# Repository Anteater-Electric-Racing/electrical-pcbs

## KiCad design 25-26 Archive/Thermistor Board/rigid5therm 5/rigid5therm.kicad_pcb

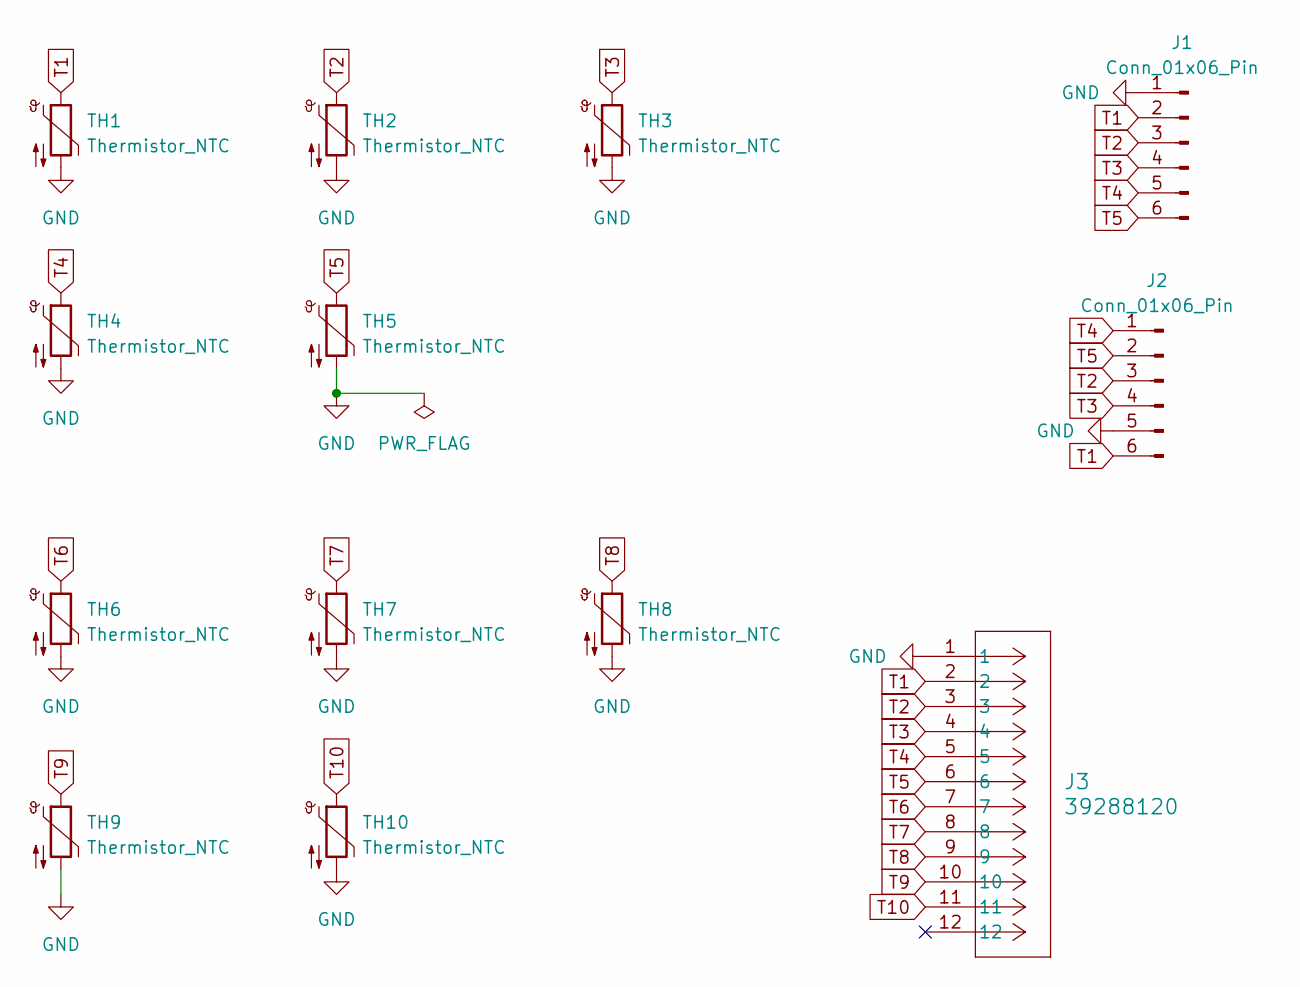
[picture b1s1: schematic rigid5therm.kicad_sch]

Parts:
J1, J2: Conn_01x06_Pin; PinHeader_2x03_P2.54mm_Vertical
J3: 39288120; CONN_SD-5566-002_12_MOL
TH1, TH2, TH3, TH4, TH5, TH6, TH7, TH8, TH9, TH10: Thermistor_NTC; Thermistor_NTCLE413

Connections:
GND: J1.1, J2.5, J3.1, TH1.2, TH2.2, TH3.2, TH4.2, TH5.2, TH6.2, TH7.2, TH8.2, TH9.2, TH10.2
T1: J1.2, J2.6, J3.2, TH1.1
T2: J1.3, J2.3, J3.3, TH2.1
T3: J1.4, J2.4, J3.4, TH3.1
T4: J1.5, J2.1, J3.5, TH4.1
T5: J1.6, J2.2, J3.6, TH5.1
T6: J3.7, TH6.1
T7: J3.8, TH7.1
T8: J3.9, TH8.1
T9: J3.10, TH9.1
T10: J3.11, TH10.1

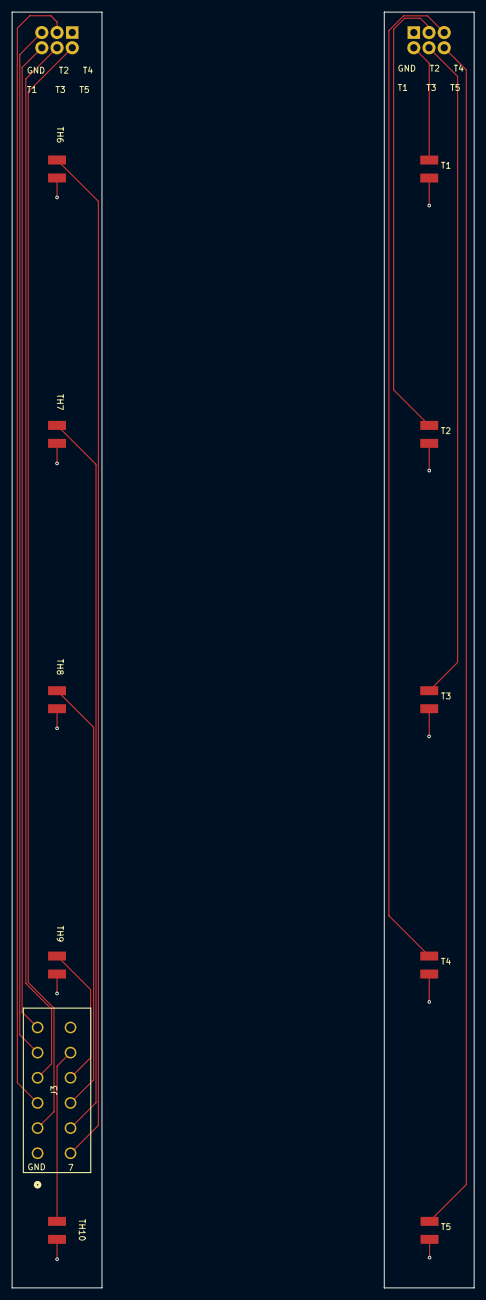
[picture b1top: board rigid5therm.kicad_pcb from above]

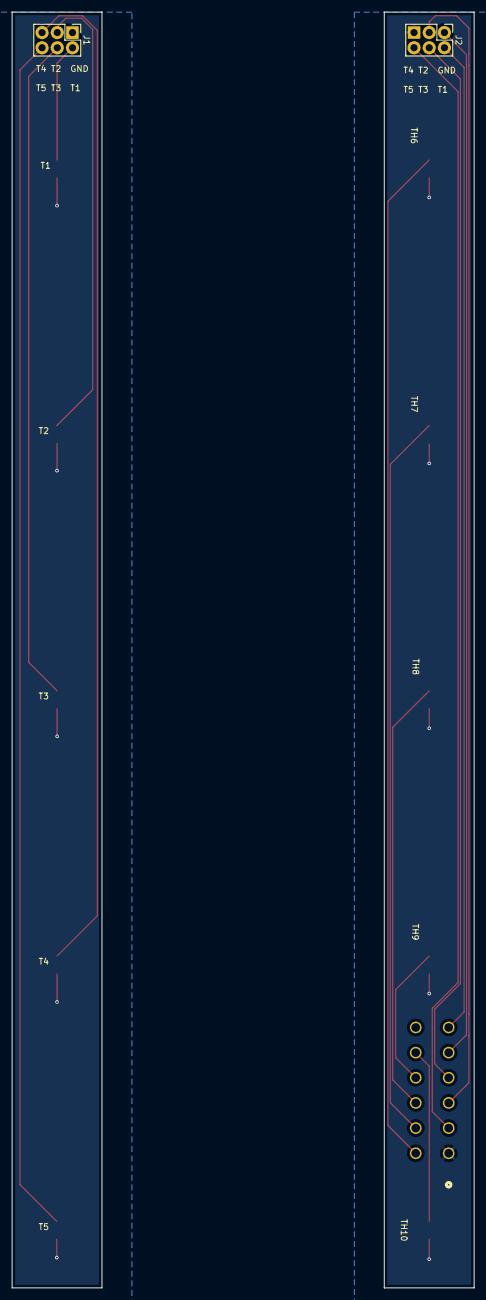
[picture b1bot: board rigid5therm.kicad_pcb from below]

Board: 2 copper layers, 77.1 x 213.0 mm, 13 parts (2 on the bottom side), 11 nets.

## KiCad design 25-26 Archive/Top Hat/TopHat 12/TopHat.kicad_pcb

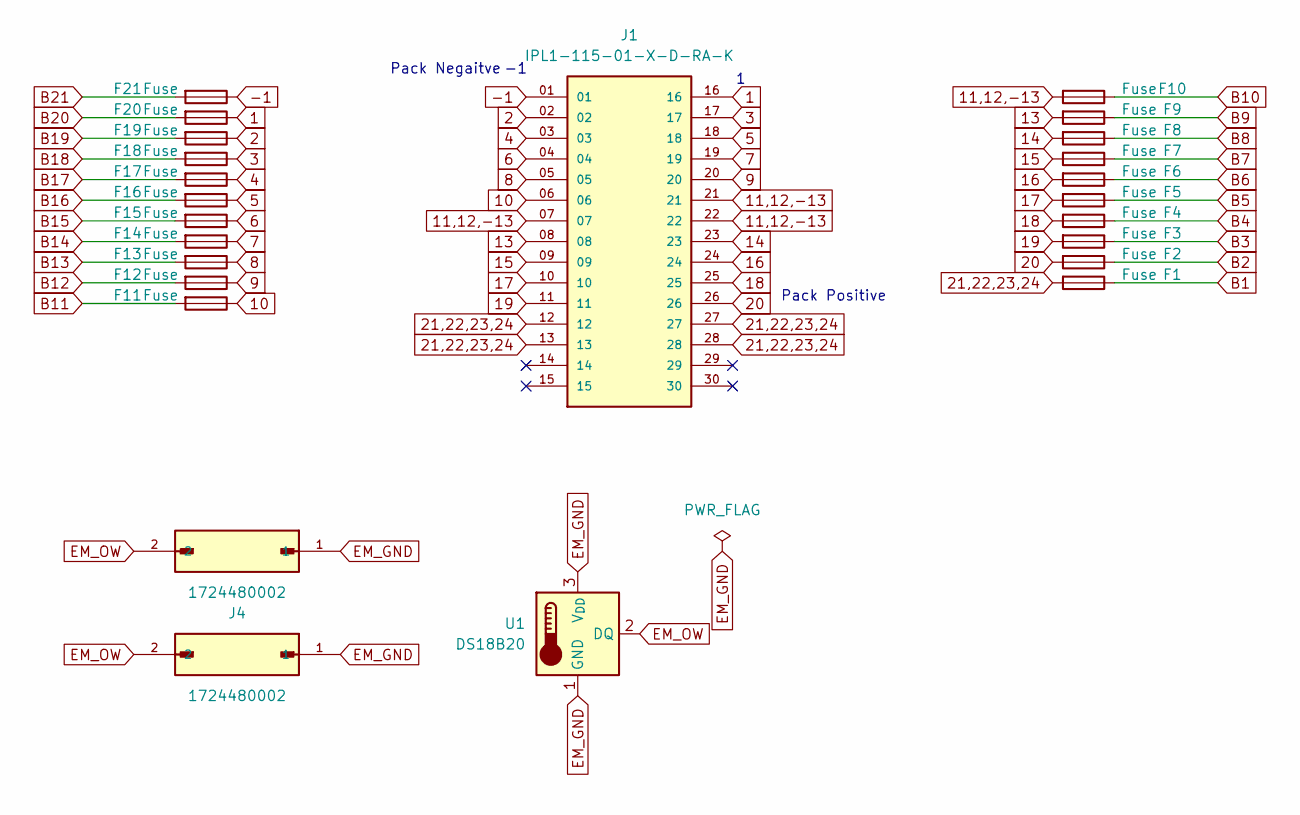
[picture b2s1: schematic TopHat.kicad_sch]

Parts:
F1, F2, F3, F4, F5, F6, F7, F8, F9, F10, F11, F12, F13, F14, F15, F16, F17, F18, F19, F20, F21: Fuse; FUSC6125X279N; MANUFACTURER PART NUMBER 0679L0500-01
J1: IPL1-115-01-X-D-RA-K; SAMTEC_IPL1-115-01-X-D-RA-K; PARTREV E
J2, J4: 1724480002; MOLEX_1724480002; PARTREV A
U1: DS18B20; TO-92_Inline; MANUFACTURER PART NUMBER Analog Devices Inc./Maxim Integrated

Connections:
1: F20.1, J1.16
2: F19.1, J1.02
3: F18.1, J1.17
4: F17.1, J1.03
5: F16.1, J1.18
6: F15.1, J1.04
7: F14.1, J1.19
8: F13.1, J1.05
9: F12.1, J1.20
10: F11.1, J1.06
11,12,-13: F10.2, J1.07, J1.21, J1.22
13: F9.2, J1.08
14: F8.2, J1.23
15: F7.2, J1.09
16: F6.2, J1.24
17: F5.2, J1.10
18: F4.2, J1.25
19: F3.2, J1.11
20: F2.2, J1.26
21,22,23,24: F1.2, J1.12, J1.13, J1.27, J1.28
-1: F21.1, J1.01
B1: F1.1
B2: F2.1
B3: F3.1
B4: F4.1
B5: F5.1
B6: F6.1
B7: F7.1
B8: F8.1
B9: F9.1
B10: F10.1
B11: F11.2
B12: F12.2
B13: F13.2
B14: F14.2
B15: F15.2
B16: F16.2
B17: F17.2
B18: F18.2
B19: F19.2
B20: F20.2
B21: F21.2
EM_GND: J2.1, J4.1, U1.1 (GND), U1.3 (V_{DD})
EM_OW: J2.2, J4.2, U1.2 (DQ)

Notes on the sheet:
Pack Negaitve
Pack Positive

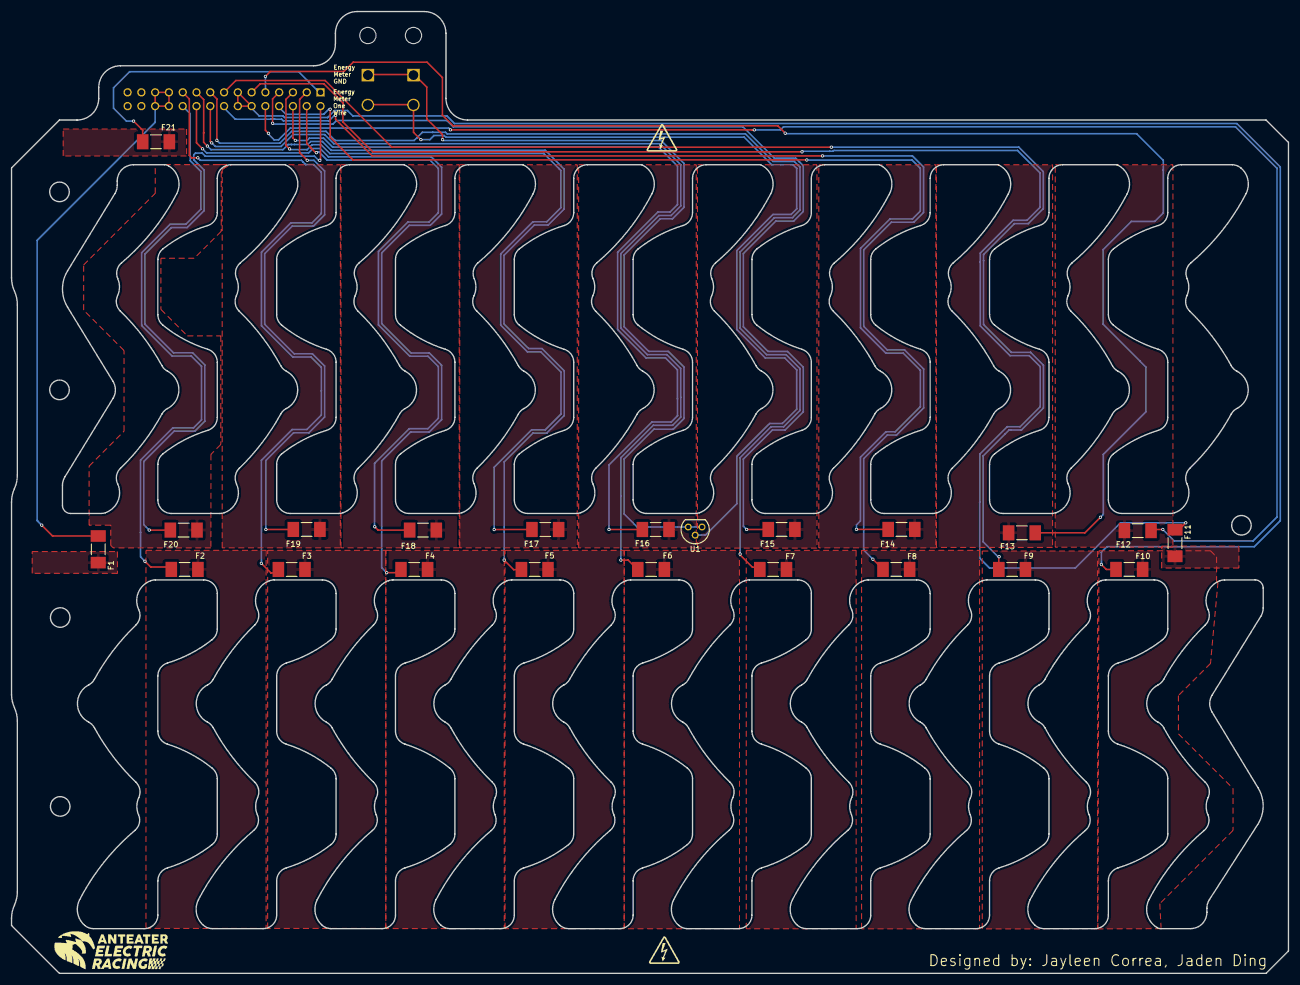
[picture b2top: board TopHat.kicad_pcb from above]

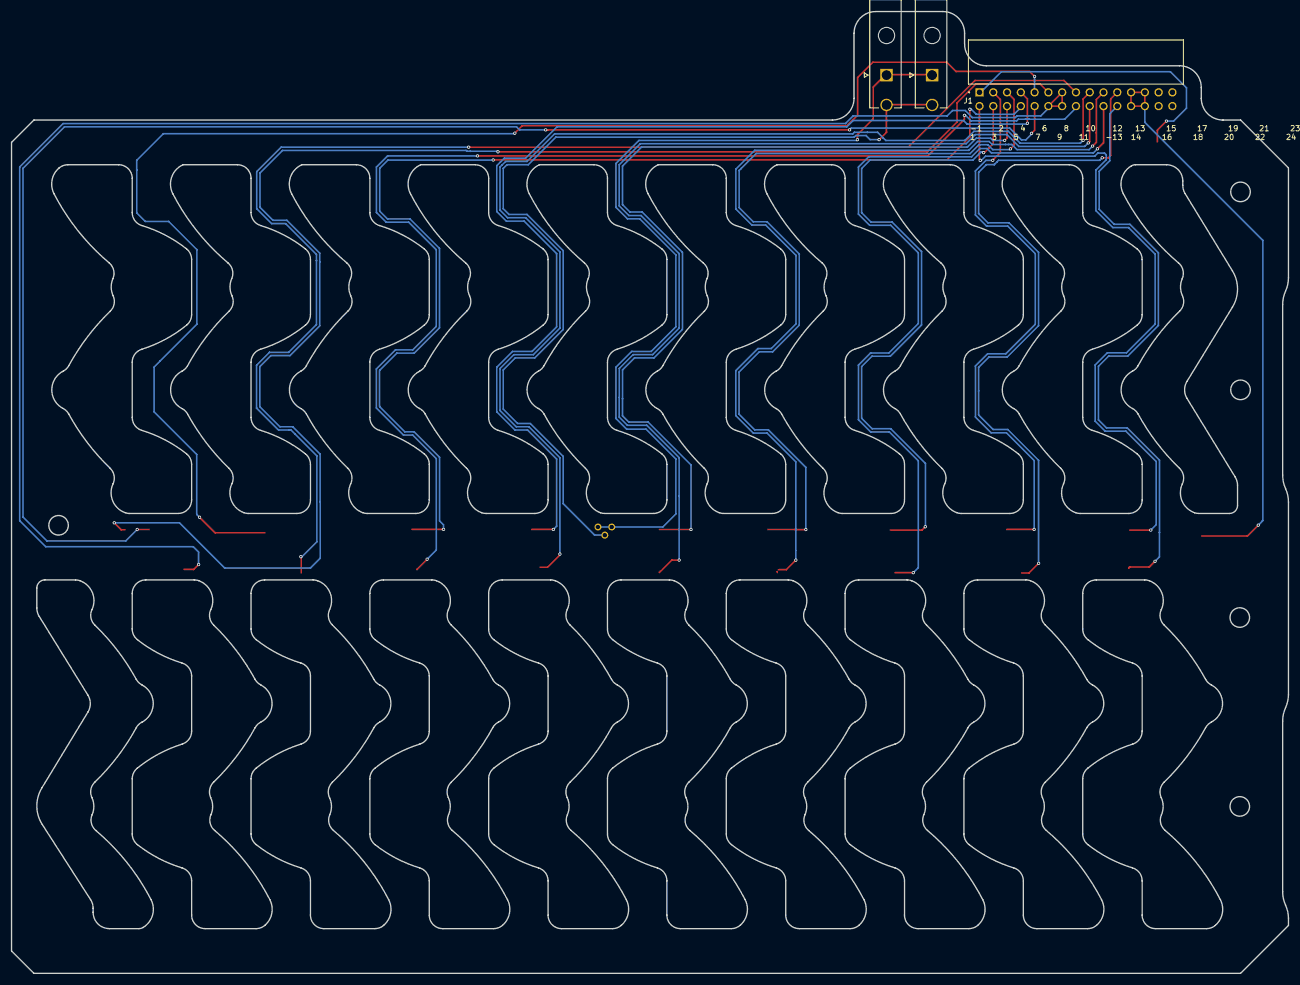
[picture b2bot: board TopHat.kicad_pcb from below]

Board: 2 copper layers, 235.4 x 177.3 mm, 25 parts (3 on the bottom side), 23 nets.

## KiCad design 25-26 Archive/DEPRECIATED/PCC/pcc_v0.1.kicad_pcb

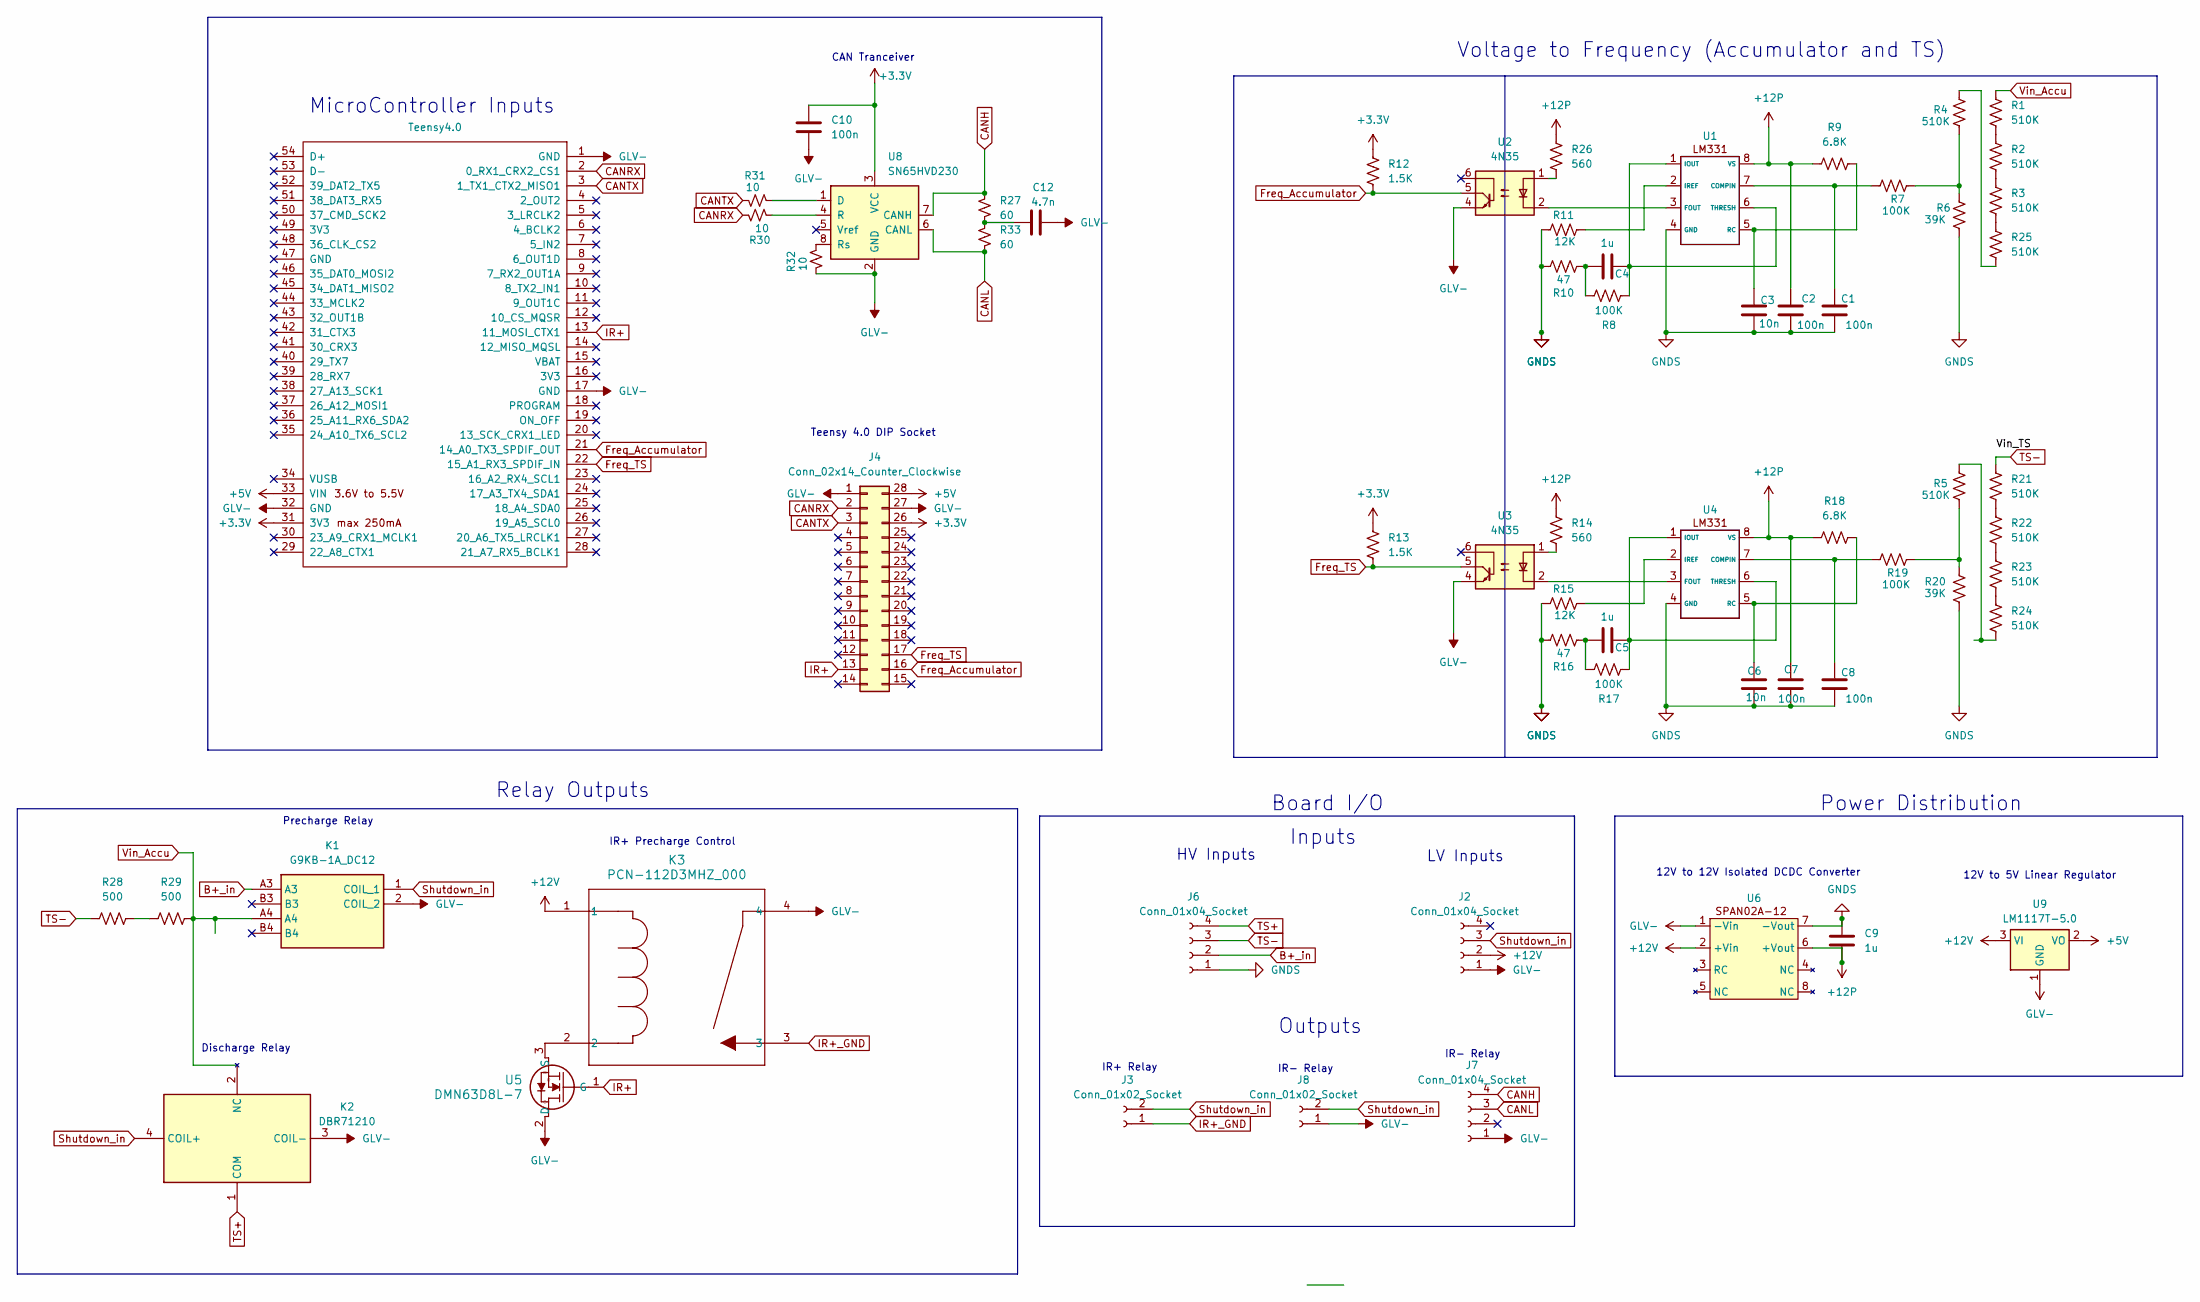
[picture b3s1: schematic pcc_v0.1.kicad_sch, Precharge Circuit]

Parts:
C1, C2, C7, C8, C10: 100n; C_0805_2012Metric
C3, C6: 10n; C_0805_2012Metric
C4, C5, C9: 1u; C_0805_2012Metric
C12: 4.7n; C_0805_2012Metric
J2, J6, J7: Conn_01x04_Socket; Molex_Mini-Fit_Jr_5566-04A2_2x02_P4.20mm_Vertical
J3, J8: Conn_01x02_Socket; Molex_Mini-Fit_Jr_5566-02A2_2x01_P4.20mm_Vertical
J4: Conn_02x14_Counter_Clockwise; DIP-28_W15.24mm_Socket
K1: G9KB-1A_DC12; G9KB1ADC12; Mouser Part Number 653-G9KB-1ADC12
K2: DBR71210; Mouser Part Number 285-DBR71210
K3: PCN-112D3MHZ_000; RELAY_PCN-105D3MHZ_000_TEC
R1, R2, R3, R4, R5, R21, R22, R23, R24, R25: 510K; R_0805_2012Metric
R6, R20: 39K; R_0805_2012Metric
R7, R8, R17, R19: 100K; R_0805_2012Metric
R9, R18: 6.8K; R_0805_2012Metric
R10, R16: 47; R_0805_2012Metric
R11, R15: 12K; R_0805_2012Metric
R12, R13: 1.5K; R_0805_2012Metric
R14, R26: 560; R_0805_2012Metric
R27, R33: 60; R_0805_2012Metric
R28, R29: 500; Ohmite HS100 500R F
R30, R31, R32: 10; R_0805_2012Metric
U1, U4: DIP-8_W7.62mm_Socket
U2, U3: 4N35; DIP-6_W7.62mm_Socket
U5: DMN63D8L-7; SOIC_63D8L-7_DIO
U6: SIP-8_19x3mm_P2.54mm
U7: Teensy4.0; DIP-28_W15.24mm_Socket
U8: SN65HVD230; SOIC-8_3.9x4.9mm_P1.27mm
U9: LM1117T-5.0; TO-220-3_Horizontal_TabDown

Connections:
+3.3V: C10.1, J4.26, R12.2, R13.2, U7.31 (3V3), U8.3 (VCC)
+5V: J4.28, U7.33 (VIN), U9.2 (VO)
+12P: C2.1, C7.1, C9.2, R9.1, R14.1, R18.1, R26.1, U1.8 (VS), U4.8 (VS), U6.6 (+Vout)
+12V: J2.2, K3.1, U6.2 (+Vin), U9.3 (VI)
B+_in: J6.2, K1.A3
CANH: J7.4, R27.1, U8.7 (CANH)
CANL: J7.3, R33.2, U8.6 (CANL)
CANRX: J4.2, R30.1, U7.2 (0_RX1_CRX2_CS1)
CANTX: J4.3, R31.2, U7.3 (1_TX1_CTX2_MISO1)
Freq_Accumulator: J4.16, R12.1, U2.5, U7.21 (14_A0_TX3_SPDIF_OUT)
Freq_TS: J4.17, R13.1, U3.5, U7.22 (15_A1_RX3_SPDIF_IN)
GLV-: C10.2, C12.2, J2.1, J4.1, J4.27, J7.1, J8.1, K1.2 (COIL_2), K2.3 (COIL-), K3.4, R32.2, U2.4, U3.4, U5.2 (D), U6.1 (-Vin), U7.1 (GND), U7.17 (GND), U7.32 (GND), U8.2 (GND), U9.1 (GND)
GNDS: C1.2, C2.2, C3.2, C6.2, C7.2, C8.2, C9.1, J6.1, R6.2, R10.2, R11.1, R15.1, R16.2, R20.2, U1.4 (GND), U4.4 (GND), U6.7 (-Vout)
IR+: J4.13, U5.1 (G), U7.13 (11_MOSI_CTX1)
IR+_GND: J3.1, K3.3
unnamed: C4.1, R8.1, R10.1
unnamed: C5.1, R16.1, R17.1
unnamed: C12.1, R27.2, R33.1
unnamed: R1.2, R2.1
unnamed: R2.2, R3.1
unnamed: R4.2, R6.1, R7.2
unnamed: R14.2, U3.1
unnamed: R5.2, R19.2, R20.1
unnamed: R21.2, R22.1
unnamed: R22.2, R23.1
unnamed: R23.2, R24.1
unnamed: R5.1, R24.2
unnamed: R3.2, R25.1
unnamed: R4.1, R25.2
unnamed: R26.2, U2.1
unnamed: R28.2, R29.1
unnamed: C1.1, R7.1, U1.7 (COMPIN)
unnamed: U1.3 (FOUT), U2.2
unnamed: C4.2, R8.2, U1.1 (IOUT), U1.6 (THRESH)
unnamed: R11.2, U1.2 (IREF)
unnamed: C3.1, R9.2, U1.5 (RC)
unnamed: C8.1, R19.1, U4.7 (COMPIN)
unnamed: U3.2, U4.3 (FOUT)
unnamed: C5.2, R17.2, U4.1 (IOUT), U4.6 (THRESH)
unnamed: R15.2, U4.2 (IREF)
unnamed: C6.1, R18.2, U4.5 (RC)
unnamed: K3.2, U5.3 (S)
unnamed: R31.1, U8.1 (D)
unnamed: R30.2, U8.4 (R)
unnamed: R32.1, U8.8 (Rs)
Shutdown_in: J2.3, J3.2, J8.2, K1.1 (COIL_1), K2.4 (COIL+)
TS+: J6.4, K2.1 (COM)
TS-: J6.3, R21.1, R28.1
Vin_Accu: K1.A4, K2.2 (NC), R1.1, R29.2

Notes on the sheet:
Board I/O
HV Inputs
Inputs
IR+ Relay
LV Inputs
Teensy 4.0 DIP Socket
Voltage to Frequency (Accumulator and TS)
MicroController Inputs
IR- Relay
Relay Outputs
Discharge Relay
CAN Tranceiver
Precharge Relay
IR+ Precharge Control
Outputs
Power Distribution
12V to 5V Linear Regulator
12V to 12V Isolated DCDC Converter

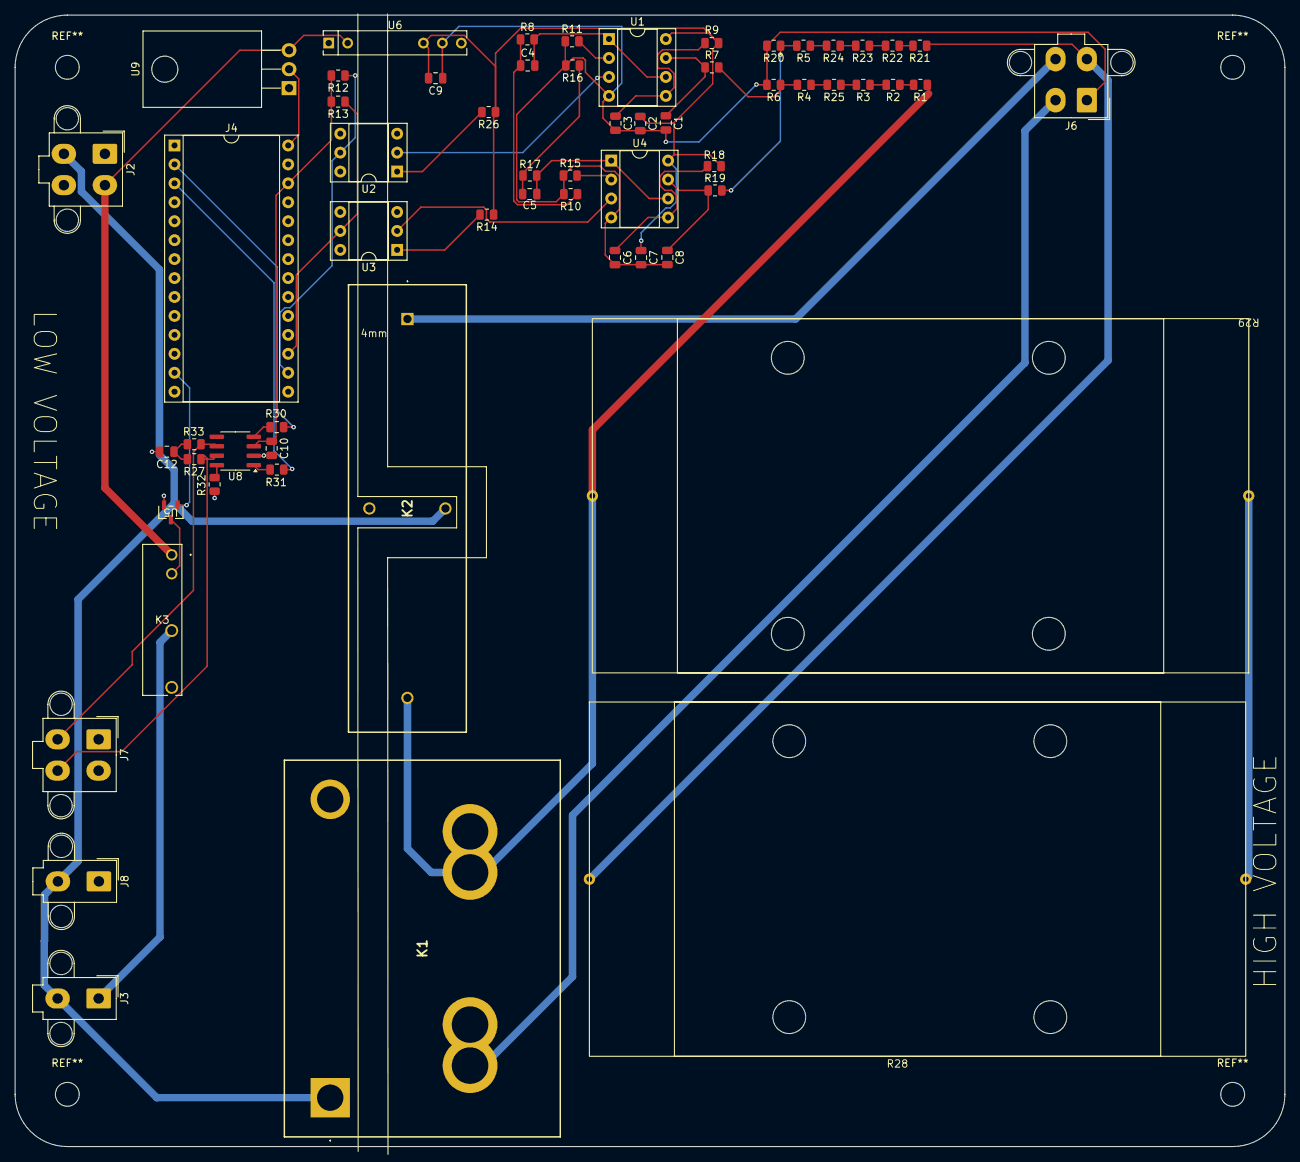
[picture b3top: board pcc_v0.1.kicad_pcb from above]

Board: 2 copper layers, 170.3 x 151.7 mm, 61 parts (0 on the bottom side), 49 nets.

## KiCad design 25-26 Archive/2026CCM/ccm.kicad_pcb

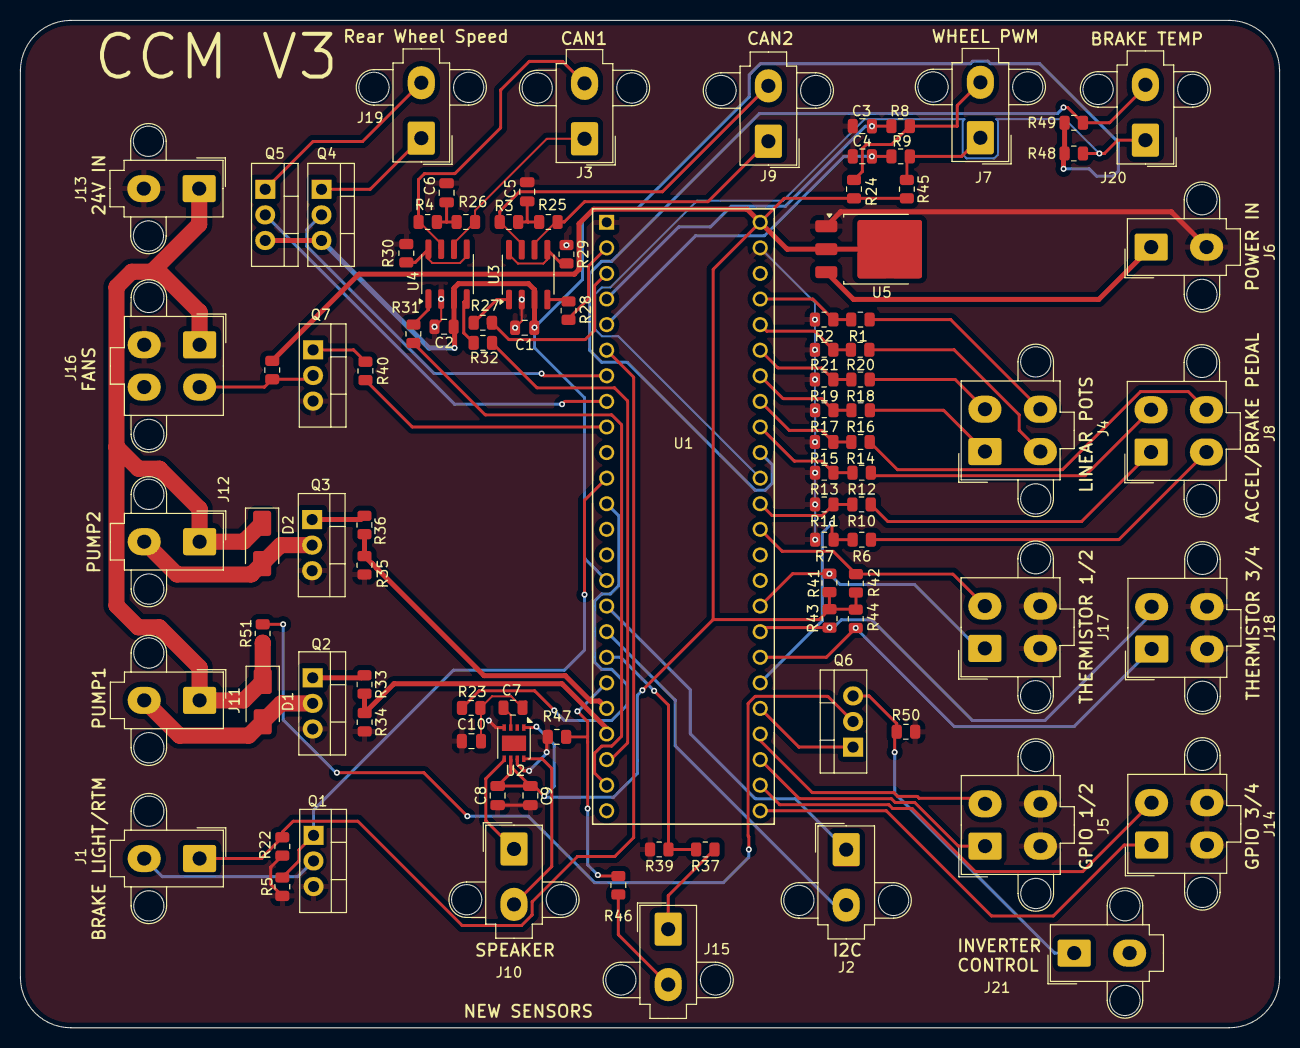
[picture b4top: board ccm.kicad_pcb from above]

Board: 2 copper layers, 125.0 x 100.0 mm, 96 parts (0 on the bottom side), 81 nets.

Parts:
C1, C2, C5, C6: 100 nF; C_0805_2012Metric
C3, C4: 0.01uF; C_0805_2012Metric
C7: 0.1uF; C_0805_2012Metric
C8: 1uF; C_0805_2012Metric
C9: 10uF; C_0805_2012Metric
C10: 10nF; C_0805_2012Metric
D1, D2: SS34; D_SMA
J1, J2, J3, J6, J7, J9, J10, J11, J12, J13, J15, J19, J20, J21: Conn_01x02_Socket; Molex_Mini-Fit_Jr_5566-02A2_2x01_P4.20mm_Vertical
J4, J5, J8, J14, J16, J17, J18: Conn_01x04_Socket; Molex_Mini-Fit_Jr_5566-04A2_2x02_P4.20mm_Vertical
Q1, Q2, Q3, Q4, Q5, Q6, Q7: IRLZ34N; TO-220-3_Vertical
R1, R6, R10, R12, R14, R16, R18, R20: 50k; R_0805_2012Metric
R2, R7, R11, R13, R15, R17, R19, R21: 97k; R_0805_2012Metric
R3, R4, R25, R26, R27, R28, R29, R30, R31, R32: 60; R_0805_2012Metric
R5, R22, R34, R35, R38, R41, R42, R43, R44, R47, R50, R51: 10k; R_0805_2012Metric
R8, R9: 10; R_0805_2012Metric
R23, R40: 1k; R_0805_2012Metric
R24, R45, R48, R49: 4.7k; R_0805_2012Metric
R33, R36: 220; R_0805_2012Metric
R37: 100k; R_0805_2012Metric
R39: 27k; R_0805_2012Metric
R46: 6.5k; R_0805_2012Metric
U1: Teensy4.1; CONN_4848-6000-CP_3MM
U2: PAM8302AAY; DFN-8-1EP_3x3mm_P0.65mm_EP1.55x2.4mm
U3, U4: SN65HVD230; SOIC-8_3.9x4.9mm_P1.27mm
U5: LM1117DT-5.0; TO-252-3_TabPin2

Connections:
+3.3V: C1.1, C2.1, Q4.3 (S), Q5.3 (S), R48.1, R49.1, U1.15 (3V3), U3.3 (VCC), U4.3 (VCC)
+5V: C8.1, C9.1, R24.2, R38.1, R41.2, R42.2, R43.2, R44.2, R45.2, U1.48 (VIN), U2.1 (~SD), U2.6 (VDD), U5.2 (VO)
CANH_1: J9.2, R3.1, U3.7 (CANH)
CANH_2: J3.2, R4.1, U4.7 (CANH)
CANL_1: J9.1, R25.2, U3.6 (CANL)
CANL_2: J3.1, R26.2, U4.6 (CANL)
CAN_RX_1: R28.1, U1.2 (0_RX1_CRX2_CS1)
CAN_RX_2: R32.1, U1.22 (30_CRX3)
CAN_TX_1: R27.1, U1.3 (1_TX1_CTX2_MISO1)
CAN_TX_2: R31.1, U1.23 (31_CTX3)
Fan+: D1.1 (K), D2.1 (K), J11.1, J12.1, J13.1, J16.1, R51.1
Fan_PWM: J16.2, Q7.2 (D), R38.2
GLV-: C1.2, C2.2, C3.2, C4.2, C5.2, C6.2, C8.2, C9.2, C10.1, J5.3, J5.4, J6.2, J13.2, J14.3, J14.4, J16.3, J17.3, J17.4, J18.3, J18.4, Q1.3 (S), Q2.3 (S), Q3.3 (S), Q7.3 (S), R2.2, R5.1, R7.2, R11.2, R13.2, R15.2, R17.2, R19.2, R21.2, R22.1, R29.1, R30.1, R34.2, R35.2, R39.2, R47.2, R50.2, U1.1 (GND), U1.47 (GND), U2.4 (IN-), U2.7 (GND), U3.2 (GND), U4.2 (GND), U5.1 (GND)
unnamed: C5.1, R3.2, R25.1
unnamed: C6.1, R4.2, R26.1
unnamed: C7.2, C10.2, R23.1
unnamed: Q1.1 (G), R5.2, U1.11 (9_OUT1C)
unnamed: Q2.1 (G), R33.1
unnamed: Q3.1 (G), R36.1
unnamed: Q4.2 (D), U1.7 (5_IN2)
unnamed: Q5.2 (D), U1.8 (6_OUT1D)
unnamed: Q6.2 (D), R51.2
unnamed: Q6.1 (G), U1.29 (37_CS)
unnamed: Q7.1 (G), R40.1
unnamed: C3.1, R8.2, U1.4 (2_OUT2)
unnamed: C4.1, R9.2, U1.5 (3_LRCLK2)
unnamed: R40.2, U1.9 (7_RX2_OUT1A)
unnamed: R10.2, R11.1, U1.37 (15_A1_RX3_SPDIF_IN)
unnamed: R12.2, R13.1, U1.40 (18_A4_SDA)
unnamed: R14.2, R15.1, U1.41 (19_A5_SCL)
unnamed: R16.2, R17.1, U1.42 (20_A6_TX5_LRCLK1)
unnamed: R18.2, R19.1, U1.43 (21_A7_RX5_BCLK1)
unnamed: R20.2, R21.1, U1.44 (22_A8_CTX1)
unnamed: R1.2, R2.1, U1.45 (23_A9_CRX1_MCLK1)
unnamed: R37.2, R39.1, U1.18 (26_A12_MOSI1)
unnamed: R46.2, R47.1, U1.19 (27_A13_SCK1)
unnamed: R35.1, R36.2, U1.20 (28_RX7)
unnamed: R33.2, R34.1, U1.21 (29_TX7)
unnamed: R6.2, R7.1, U1.30 (38_CS1_IN1)
unnamed: C7.1, U2.3 (IN+)
unnamed: R27.2, U3.1 (D)
unnamed: R28.2, U3.4 (R)
unnamed: R29.2, U3.5 (Vref), U3.8 (Rs)
unnamed: R31.2, U4.1 (D)
unnamed: R32.2, U4.4 (R)
unnamed: R30.2, U4.5 (Vref), U4.8 (Rs)
PWM_in_1: J7.1, R9.1, R45.1
PWM_in_2: J7.2, R8.1, R24.1
Pump1-: D1.2 (A), J11.2, Q2.2 (D)
Pump2-: D2.2 (A), J12.2, Q3.2 (D)
Vin: J6.1, U5.3 (VI)
acc_ped_1: J8.4, R14.1
acc_ped_2: J8.2, R12.1
brake_1: J8.1, R10.1
brake_2: J8.3, R6.1
brake_light: J1.2, Q1.2 (D)
brake_temp_scl: J20.1, R48.2, U1.38 (16_A2_RX4_SCL1)
brake_temp_sda: J20.2, R49.2, U1.39 (17_A3_TX4_SDA1)
gpio1: J5.2, U1.28 (36_CS)
gpio2: J5.1, U1.27 (35_TX8)
gpio3: J14.2, U1.26 (34_RX8)
gpio4: J14.1, U1.25 (33_MCLK2)
i2c_SCL: J2.1, U1.16 (24_A10_TX6_SCL2)
i2c_SDA: J2.2, U1.17 (25_A11_RX6_SDA2)
kl15: J21.1, Q6.3 (S), R50.1
lin_pot_1: J4.4, R1.1
lin_pot_2: J4.3, R20.1
lin_pot_3: J4.2, R18.1
lin_pot_4: J4.1, R16.1
ready_to_drive_button: J1.1, R22.2, U1.6 (4_BCLK2)
shock_travel: J15.2, R46.1
speaker+: J10.1, U2.5 (OUT+)
speaker-: J10.2, U2.8 (OUT-)
speaker_pwm: R23.2, U1.12 (10_CS_MQSR)
steering_angle: J15.1, R37.1
thermistor1+: J17.2, R41.1, U1.36 (14_A0_TX3_SPDIF_OUT)
thermistor2+: J17.1, R42.1, U1.33 (41_A17)
thermistor3+: J18.2, R43.1, U1.32 (40_A16)
thermistor4+: J18.1, R44.1, U1.31 (39_MISO1_OUT1A)
wheelspeed1: J19.1, Q4.1 (G)
wheelspeed2: J19.2, Q5.1 (G)
